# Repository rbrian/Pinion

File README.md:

# Pinion
Pinion™ is a new series of expansion boards compatible with the Adafruit Feather format. They include a strip of tied pins for each Feather pin, similar to a traditional breadboard, as well as a 3.3v power bus, and busses for both SDI and I2C. This makes it easier to build a prototype or one-off circuit using breakout boards without ending up in a ratsnest of I2C cables and jumpter wires. There are also spots to mount a 0.1" pitch screw terminal for both 3.3v and 5V power, for those cases where power via the Feather's USB port isn't the best solution. Keep in mind that the 5V input is tied directly to the Feather's USB, so it will probably back-power the USB connection and potentially cause damage to your PC. You have been warned. 

There are current 2 boards in the Pinion series, Pinion One for a single Feather, and Pinion 2 for a Feather and associated Featherwing.

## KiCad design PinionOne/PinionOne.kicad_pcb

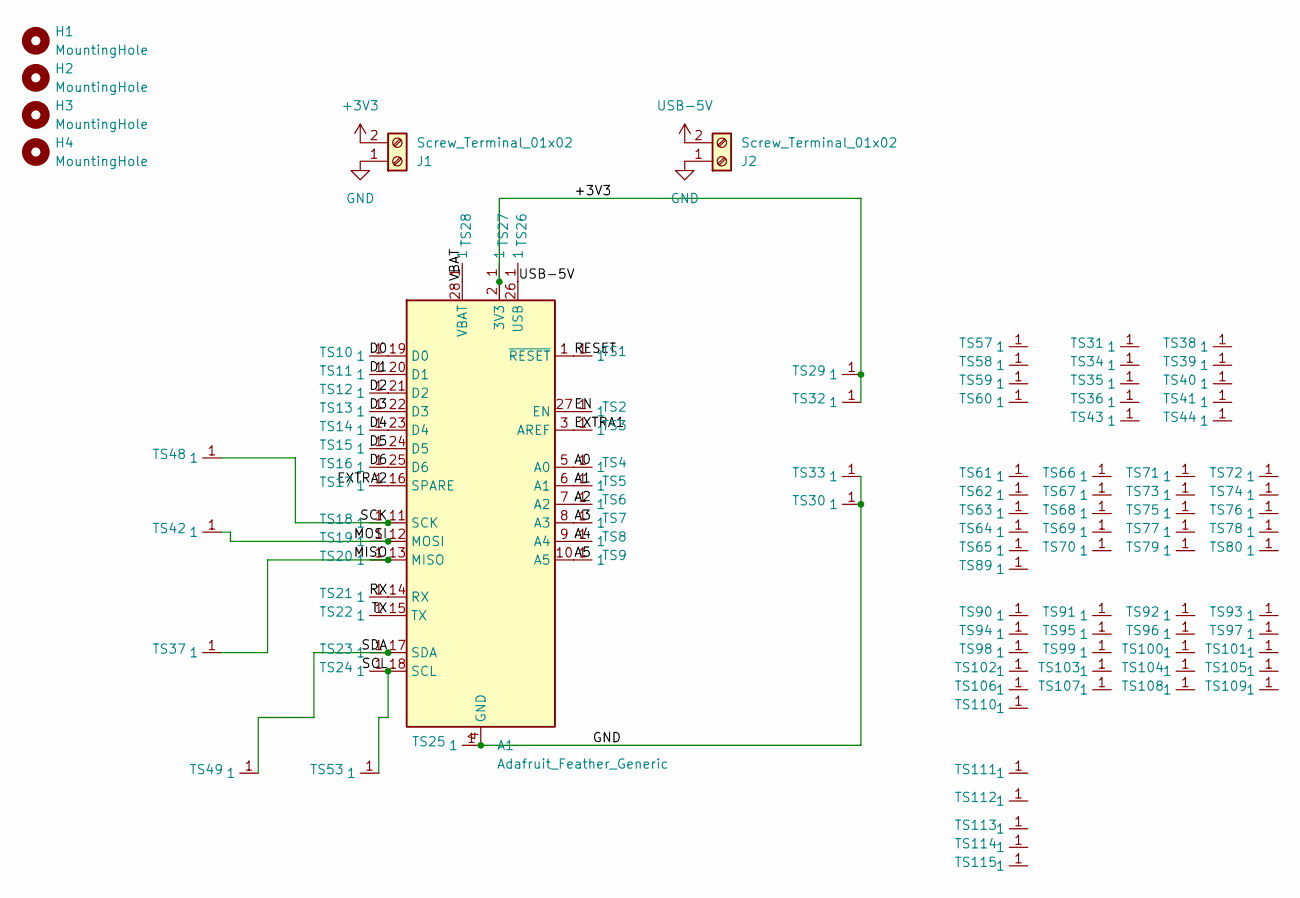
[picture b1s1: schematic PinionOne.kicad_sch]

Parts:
A1: Adafruit_Feather_Generic; Adafruit_Feather
H1, H2, H3, H4: MountingHole; MountingHole_2.5mm_Pad_TopBottom
J1, J2: Screw_Terminal_01x02; TerminalBlock_screw_2.54_left
TS1, TS2, TS3, TS4, TS5, TS6, TS7, TS8, TS9, TS10, TS11, TS12, TS13, TS14, TS15, TS16, TS17, TS18, TS19, TS20, TS21, TS22, TS23, TS24, TS25, TS26, TS27, TS28: TieStrip-5
TS29, TS30, TS32, TS33, TS37, TS42, TS48, TS49, TS53: TieStrip-21
TS31, TS34, TS35, TS36, TS38, TS39, TS40, TS41, TS43, TS44, TS57, TS58, TS59, TS60: TieStrip-6
TS61, TS62, TS63, TS64, TS65, TS66, TS67, TS68, TS69, TS70, TS71, TS72, TS73, TS74, TS75, TS76, TS77, TS78, TS79, TS80, TS89, TS90, TS91, TS92, TS93, TS94, TS95, TS96, TS97, TS98, TS99, TS100, TS101, TS102, TS103, TS104, TS105, TS106, TS107, TS108, TS109, TS110: TieStrip-3
TS111, TS112, TS113, TS114, TS115: TieStrip-7

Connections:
+3V3: A1.2 (3V3), J1.2, TS27.1, TS29.1, TS32.1
/A0: A1.5 (A0), TS4.1
/A1: A1.6 (A1), TS5.1
/A2: A1.7 (A2), TS6.1
/A3: A1.8 (A3), TS7.1
/A4: A1.9 (A4), TS8.1
/A5: A1.10 (A5), TS9.1
/D0: A1.19 (D0), TS10.1
/D1: A1.20 (D1), TS11.1
/D2: A1.21 (D2), TS12.1
/D3: A1.22 (D3), TS13.1
/D4: A1.23 (D4), TS14.1
/D5: A1.24 (D5), TS15.1
/D6: A1.25 (D6), TS16.1
/EN: A1.27 (EN), TS2.1
/EXTRA1: A1.3 (AREF), TS3.1
/EXTRA2: A1.16 (SPARE), TS17.1
/MISO: A1.13 (MISO), TS20.1, TS37.1
/MOSI: A1.12 (MOSI), TS19.1, TS42.1
/RESET: A1.1 (~RESET), TS1.1
/RX: A1.14 (RX), TS21.1
/SCK: A1.11 (SCK), TS18.1, TS48.1
/SCL: A1.18 (SCL), TS24.1, TS53.1
/SDA: A1.17 (SDA), TS23.1, TS49.1
/TX: A1.15 (TX), TS22.1
/VBAT: A1.28 (VBAT), TS28.1
GND: A1.4 (GND), J1.1, J2.1, TS25.1, TS30.1, TS33.1
USB-5V: A1.26 (USB), J2.2, TS26.1

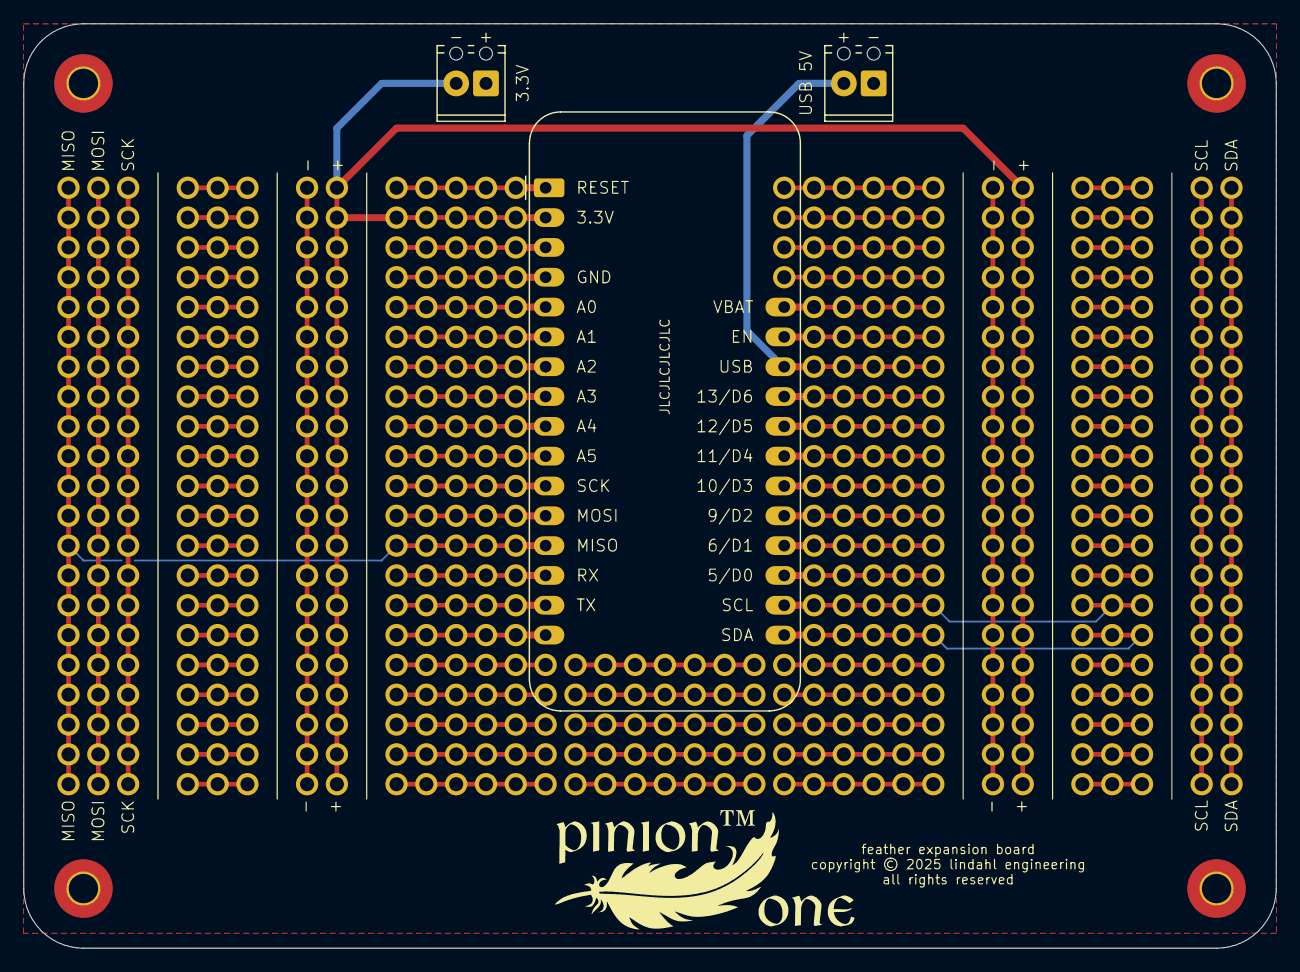
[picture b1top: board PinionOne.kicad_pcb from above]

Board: 2 copper layers, 106.7 x 78.7 mm, 105 parts (0 on the bottom side), 28 nets.

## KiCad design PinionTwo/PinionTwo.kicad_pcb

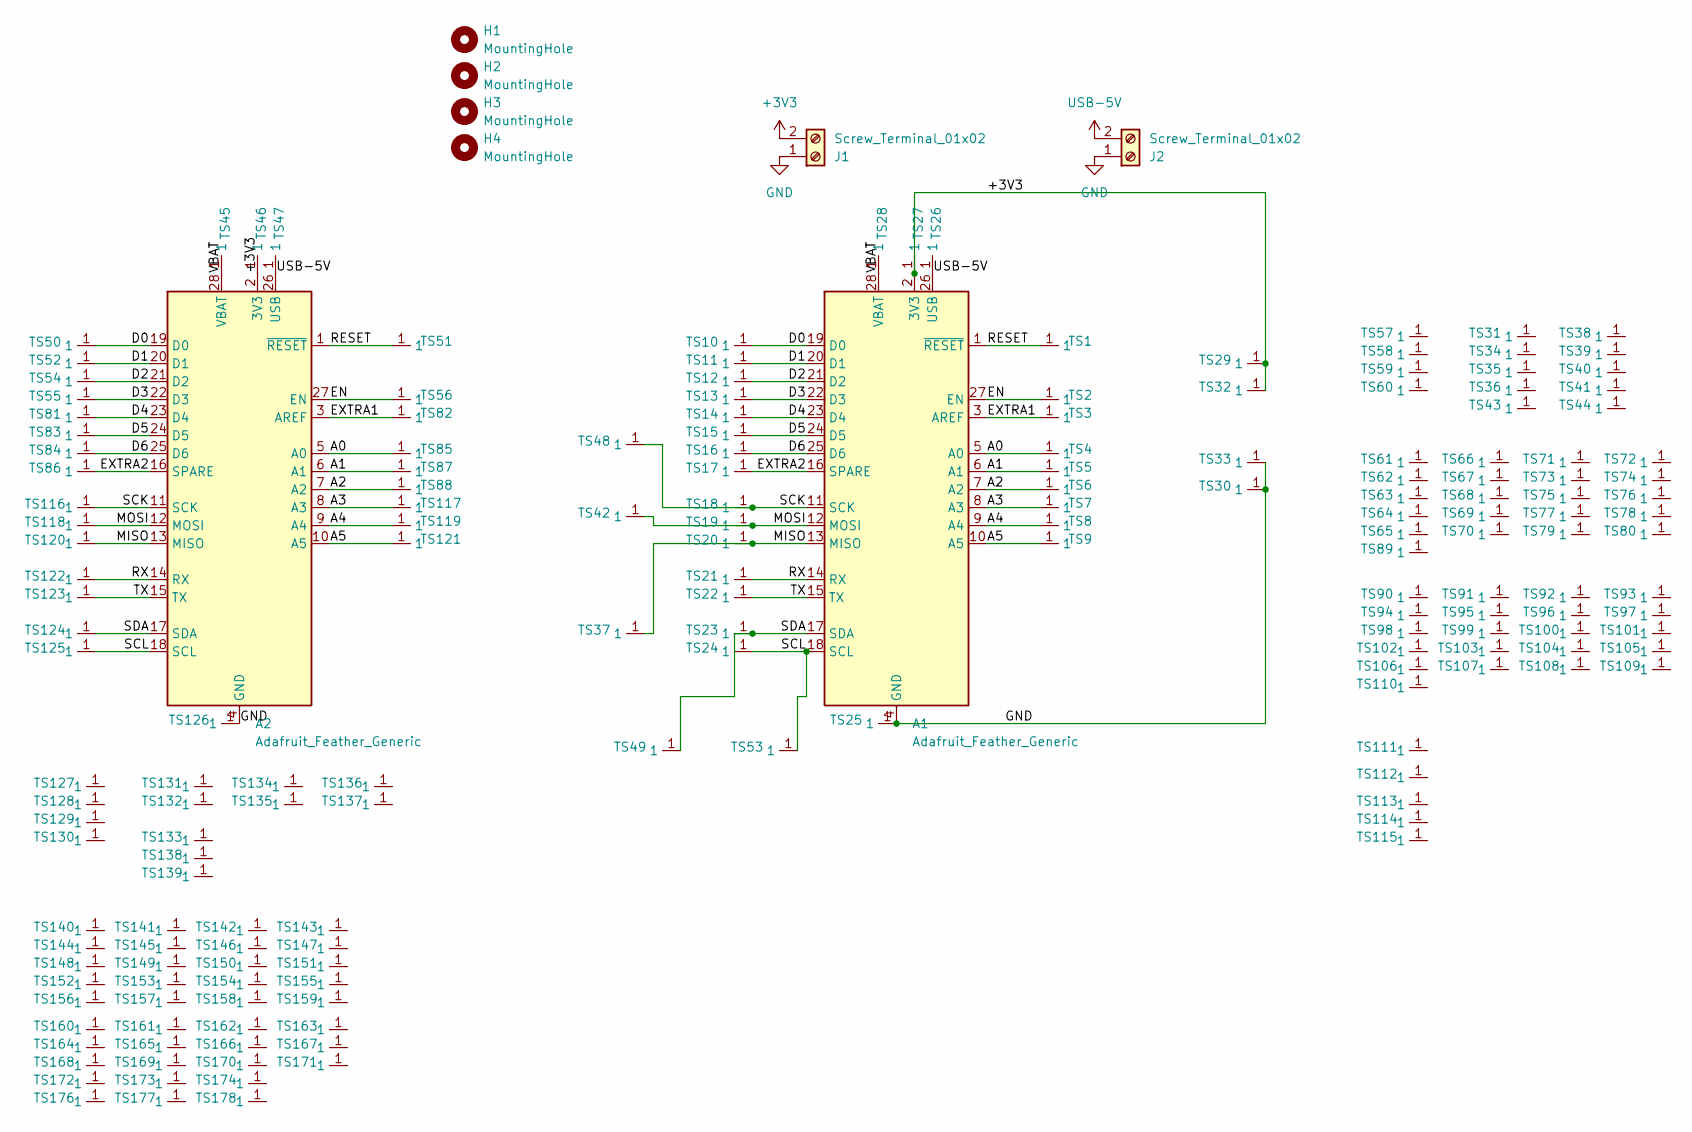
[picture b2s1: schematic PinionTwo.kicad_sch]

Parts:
A1, A2: Adafruit_Feather_Generic; Adafruit_Feather
H1, H2, H3, H4: MountingHole; MountingHole_2.5mm_Pad_TopBottom
J1, J2: Screw_Terminal_01x02; TerminalBlock_screw_2.54_left
TS1, TS2, TS3, TS4, TS5, TS6, TS7, TS8, TS9, TS10, TS11, TS12, TS13, TS14, TS15, TS16, TS17, TS18, TS19, TS20, TS21, TS22, TS23, TS24, TS25, TS26, TS27, TS28, TS45, TS46, TS47, TS50, TS51, TS52, TS54, TS55, TS56, TS81, TS82, TS83, TS84, TS85, TS86, TS87, TS88, TS116, TS117, TS118, TS119, TS120, TS121, TS122, TS123, TS124, TS125, TS126: TieStrip-5
TS29, TS30, TS32, TS33, TS37, TS42, TS48, TS49, TS53: TieStrip-40
TS31, TS34, TS35, TS36, TS38, TS39, TS40, TS41, TS43, TS44, TS57, TS58, TS59, TS60, TS127, TS128, TS129, TS130, TS131, TS132, TS134, TS135, TS136, TS137: TieStrip-6
TS61, TS62, TS63, TS64, TS65, TS66, TS67, TS68, TS69, TS70, TS71, TS72, TS73, TS74, TS75, TS76, TS77, TS78, TS79, TS80, TS89, TS90, TS91, TS92, TS93, TS94, TS95, TS96, TS97, TS98, TS99, TS100, TS101, TS102, TS103, TS104, TS105, TS106, TS107, TS108, TS109, TS110, TS140, TS141, TS142, TS143, TS144, TS145, TS146, TS147, TS148, TS149, TS150, TS151, TS152, TS153, TS154, TS155, TS156, TS157, TS158, TS159, TS160, TS161, TS162, TS163, TS164, TS165, TS166, TS167, TS168, TS169, TS170, TS171, TS172, TS173, TS174, TS176, TS177, TS178: TieStrip-3
TS111, TS112, TS113, TS114, TS115, TS133, TS138, TS139: TieStrip-7

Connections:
+3V3: A1.2 (3V3), A2.2 (3V3), J1.2, TS27.1, TS29.1, TS32.1, TS46.1
/A0: A1.5 (A0), A2.5 (A0), TS4.1, TS85.1
/A1: A1.6 (A1), A2.6 (A1), TS5.1, TS87.1
/A2: A1.7 (A2), A2.7 (A2), TS6.1, TS88.1
/A3: A1.8 (A3), A2.8 (A3), TS7.1, TS117.1
/A4: A1.9 (A4), A2.9 (A4), TS8.1, TS119.1
/A5: A1.10 (A5), A2.10 (A5), TS9.1, TS121.1
/D0: A1.19 (D0), A2.19 (D0), TS10.1, TS50.1
/D1: A1.20 (D1), A2.20 (D1), TS11.1, TS52.1
/D2: A1.21 (D2), A2.21 (D2), TS12.1, TS54.1
/D3: A1.22 (D3), A2.22 (D3), TS13.1, TS55.1
/D4: A1.23 (D4), A2.23 (D4), TS14.1, TS81.1
/D5: A1.24 (D5), A2.24 (D5), TS15.1, TS83.1
/D6: A1.25 (D6), A2.25 (D6), TS16.1, TS84.1
/EN: A1.27 (EN), A2.27 (EN), TS2.1, TS56.1
/EXTRA1: A1.3 (AREF), A2.3 (AREF), TS3.1, TS82.1
/EXTRA2: A1.16 (SPARE), A2.16 (SPARE), TS17.1, TS86.1
/MISO: A1.13 (MISO), A2.13 (MISO), TS20.1, TS37.1, TS120.1
/MOSI: A1.12 (MOSI), A2.12 (MOSI), TS19.1, TS42.1, TS118.1
/RESET: A1.1 (~RESET), A2.1 (~RESET), TS1.1, TS51.1
/RX: A1.14 (RX), A2.14 (RX), TS21.1, TS122.1
/SCK: A1.11 (SCK), A2.11 (SCK), TS18.1, TS48.1, TS116.1
/SCL: A1.18 (SCL), A2.18 (SCL), TS24.1, TS53.1, TS125.1
/SDA: A1.17 (SDA), A2.17 (SDA), TS23.1, TS49.1, TS124.1
/TX: A1.15 (TX), A2.15 (TX), TS22.1, TS123.1
/VBAT: A1.28 (VBAT), A2.28 (VBAT), TS28.1, TS45.1
GND: A1.4 (GND), A2.4 (GND), J1.1, J2.1, TS25.1, TS30.1, TS33.1, TS126.1
USB-5V: A1.26 (USB), A2.26 (USB), J2.2, TS26.1, TS47.1

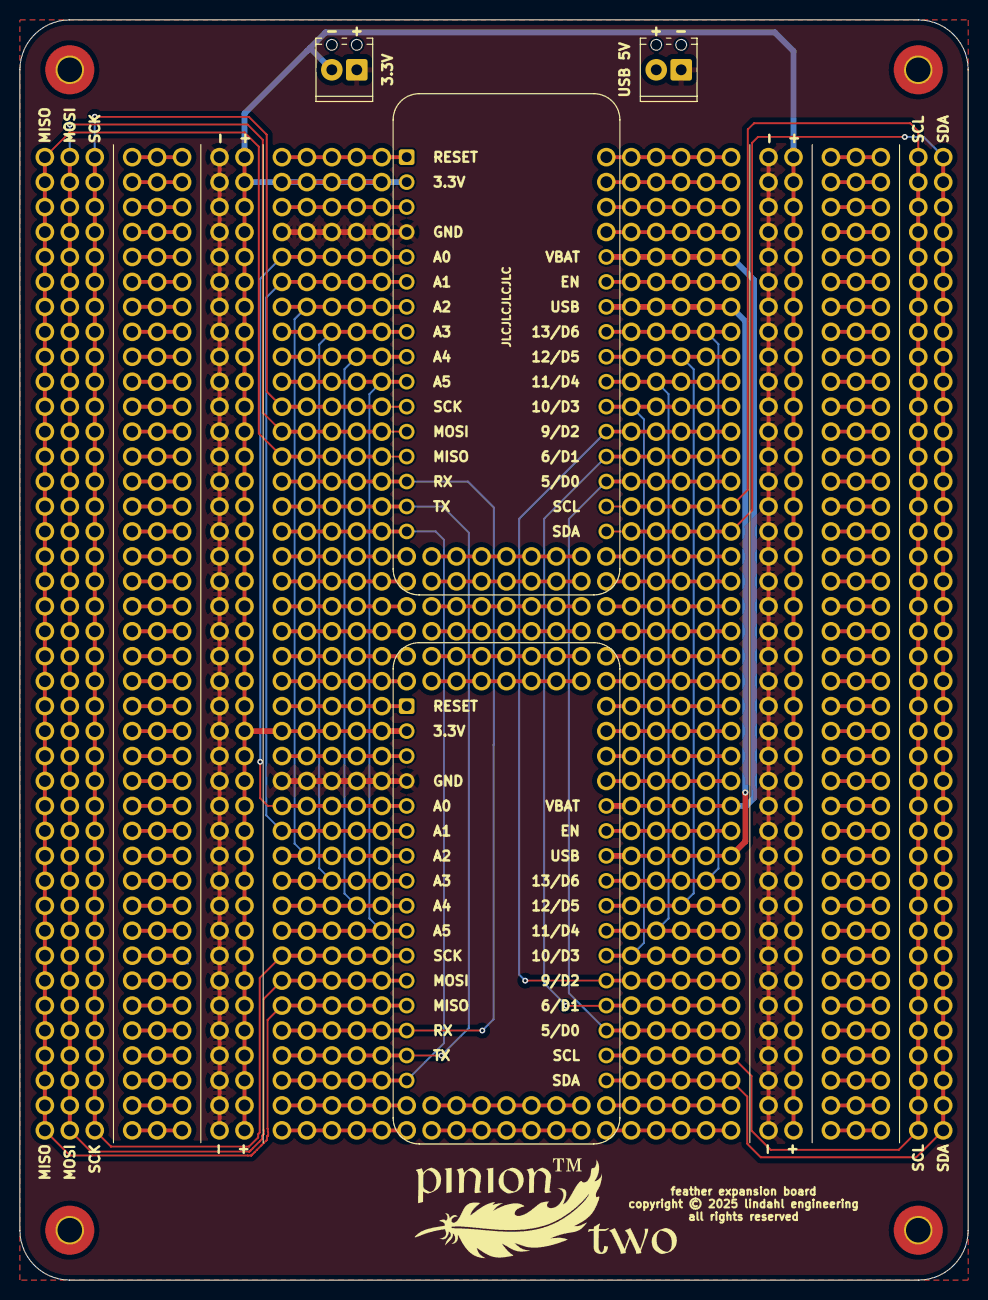
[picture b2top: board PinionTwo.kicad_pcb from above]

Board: 2 copper layers, 96.5 x 128.3 mm, 185 parts (0 on the bottom side), 28 nets.

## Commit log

2025-07-02 Add readme
2025-07-05 Rename to one/two

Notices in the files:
PinionOne/PinionOne.kicad_pcb:
copyright © 2025 lindahl engineering
all rights reserved
